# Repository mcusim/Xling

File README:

hardware
	3d_models	.STEP and .WRL model files for all footprints
	datasheets	data sheets for components used
	gerber		final production files
	images		SVG images and 3D board renders
	lib_sch		schematic symbols
	lib_fp.pretty	footprints
	pdf		schematics, board layouts, dimension drawings

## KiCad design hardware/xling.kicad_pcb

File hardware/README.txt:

3d_models	.STEP and .WRL model files for all footprints
datasheets	data sheets for components used
gerber		final production files
images		SVG images and 3D board renders
lib_sch		schematic symbols
lib_fp.pretty	footprints
pdf		schematics, board layouts, dimension drawings

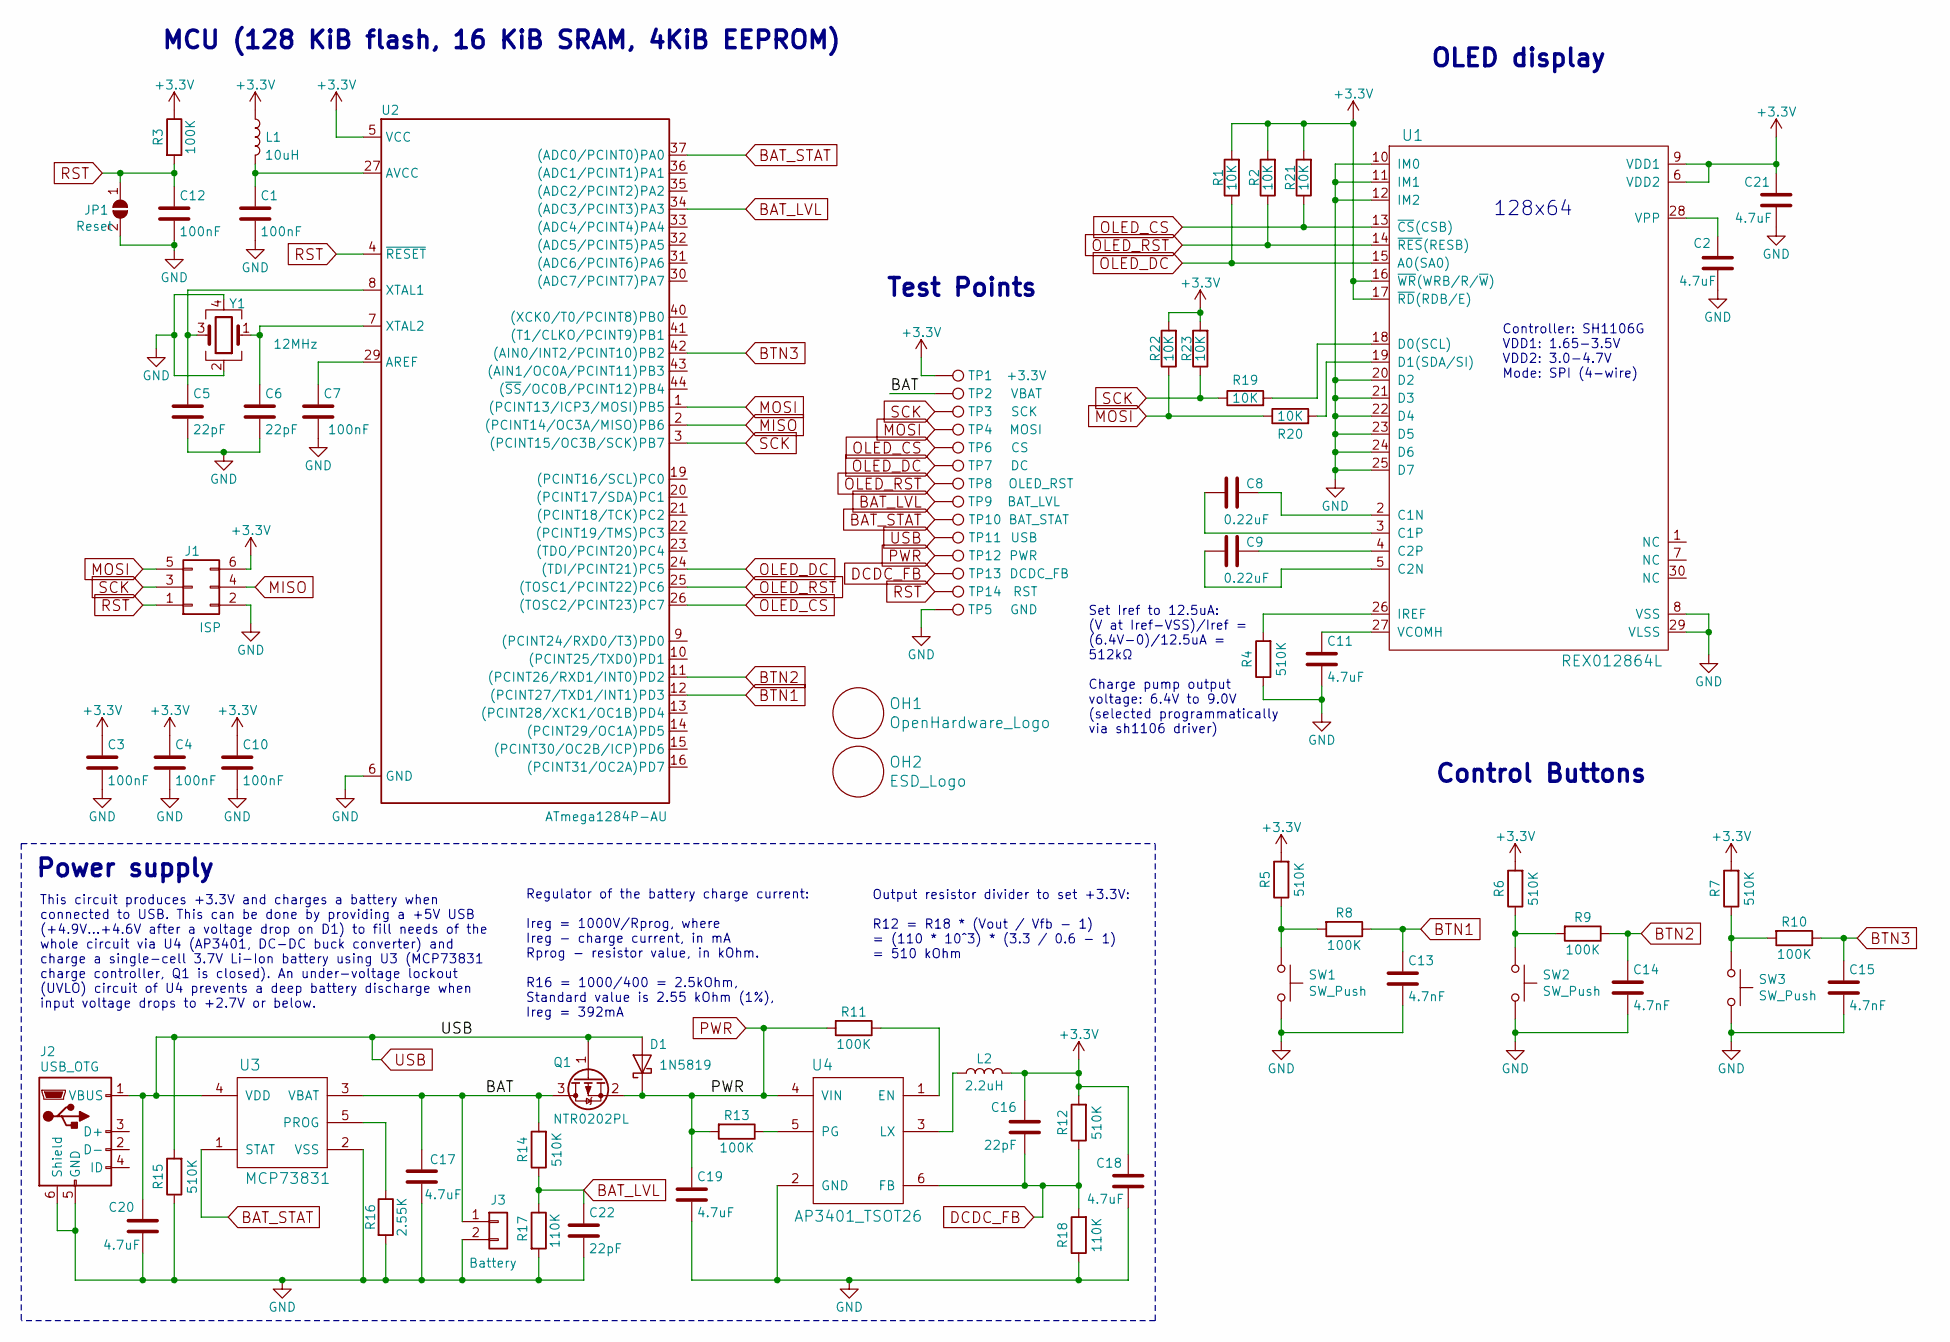
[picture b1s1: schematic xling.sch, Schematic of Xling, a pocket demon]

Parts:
C1, C3, C4, C7, C10, C12: 100nF; C_0603_1608Metric; MPN CL10B104KO8NNNC
C2, C11, C17, C18, C19, C20, C21: 4.7uF; C_0603_1608Metric; MPN CL10A475KQ8NNNC
C5, C6, C16, C22: 22pF; C_0603_1608Metric; MPN CL10C220JB8NNNC
C8, C9: 0.22uF; C_0603_1608Metric; MPN CL10B224KO8NNNC
C13, C14, C15: 4.7nF; C_0603_1608Metric; MPN CL10B472KB8NNNC
D1: 1N5819; D_SOD-123; MPN 1N5819HW-7-F
J1: ISP; Molex_Pico-Lock_504050-0691_1x06-1MP_P1.50mm_Horizontal; MPN 504050-0691
J2: USB_OTG; USB_Micro-B_Molex-105017-0001; MPN 105017-0001
J3: Battery; Battery_SMD_pads_1x02_HandSoldering; MPN N/A
JP1: Reset; SolderJumper-2_P1.3mm_Open_Pad1.0x1.5mm
L1: 10uH; L_1210_3225Metric; MPN B82422A1103K100
L2: 2.2uH; L_1210_3225Metric; MPN NLV32T-2R2J-PF
OH1: OpenHardware_Logo; OSHW-Logo_5.7x6mm_SilkScreen
OH2: ESD_Logo; ESD-Logo_6.6x6mm_SilkScreen
Q1: NTR0202PL; SOT-23; MPN NTR0202PLT1G
R1, R2, R19, R20, R21, R22, R23: 10K; R_0603_1608Metric; MPN 0603SAJ0103T5E
R3, R8, R9, R10, R11, R13: 100K; R_0603_1608Metric; MPN 0603SAJ0104T5E
R4, R5, R6, R7, R12, R14, R15: 510K; R_0603_1608Metric; MPN 0603SAJ0514T5E
R16: 2.55K; R_0603_1608Metric; MPN 0603SAF2551T5E
R17, R18: 110K; R_0603_1608Metric; MPN 0603SAF1103T5E
SW1, SW2, SW3: SW_Push; SW_Tact_4.5x4.5mm_TVCM09BB_Low_Profile; MPN TVCM09BB
TP1: +3.3V; TestPoint_Pad_D0.5mm
TP2: VBAT; TestPoint_Pad_D0.5mm
TP3: SCK; TestPoint_Pad_D0.5mm
TP4: MOSI; TestPoint_Pad_D0.5mm
TP5: GND; TestPoint_Pad_D1.0mm
TP6: CS; TestPoint_Pad_D0.5mm
TP7: DC; TestPoint_Pad_D0.5mm
TP8: OLED_RST; TestPoint_Pad_D0.5mm
TP9: BAT_LVL; TestPoint_Pad_D0.5mm
TP10: BAT_STAT; TestPoint_Pad_D0.5mm
TP11: USB; TestPoint_Pad_D0.5mm
TP12: PWR; TestPoint_Pad_D0.5mm
TP13: DCDC_FB; TestPoint_Pad_D0.5mm
TP14: RST; TestPoint_Pad_D0.5mm
U1: REX012864L; DisplayPin_1x30_P0.7mm; MPN REX012864LWAP3N00000
U2: ATmega1284P-AU; TQFP-44_10x10mm_P0.8mm; MPN ATMEGA1284P-AU
U3: MCP73831; MCP73831_SOT_23; MPN MCP73831T-2ATI/OT
U4: AP3401_TSOT26; MPN AP3401KTTR-G1
Y1: 12MHz; Crystal_SMD_CFPX-104-4Pin_5x3.2mm; MPN LFXTAL032878BULK

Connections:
+3V3: C3.1, C4.1, C10.1, C16.1, C18.1, C21.1, J1.6, L1.1, L2.2, R1.2, R2.2, R3.1, R5.2, R6.2, R7.2, R12.2, R21.2, R22.2, R23.2, TP1.1, U1.6 (VDD2), U1.9 (VDD1), U1.16 (~WR~(WRB/R/~W~)), U1.17 (~RD~(RDB/E)), U2.5 (VCC), U2.17 (VCC), U2.38 (VCC)
/BAT: C17.1, J3.1, Q1.3 (D), R14.2, TP2.1, U3.3 (VBAT)
BAT_LVL: C22.2, R14.1, R17.1, TP9.1, U2.34 ((ADC3/PCINT3)PA3)
BAT_STAT: TP10.1, U2.37 ((ADC0/PCINT0)PA0), U3.1 (STAT)
BTN1: C13.1, R8.1, U2.12 ((PCINT27/TXD1/INT1)PD3)
BTN2: C14.1, R9.1, U2.11 ((PCINT26/RXD1/INT0)PD2)
BTN3: C15.1, R10.1, U2.42 ((AIN0/INT2/PCINT10)PB2)
DCDC_FB: C16.2, R12.1, R18.2, TP13.1, U4.6 (FB)
GND: C1.2, C2.2, C3.2, C4.2, C5.1, C6.1, C7.2, C10.2, C11.2, C12.2, C13.2, C14.2, C15.2, C17.2, C18.2, C19.2, C20.2, C21.2, C22.1, J1.2, J2.5 (GND), J2.6 (Shield), J3.2, JP1.2 (B), R4.1, R15.1, R16.2, R17.2, R18.1, SW1.2, SW2.2, SW3.2, TP5.1, U1.8 (VSS), U1.10 (IM0), U1.11 (IM1), U1.12 (IM2), U1.20 (D2), U1.21 (D3), U1.22 (D4), U1.23 (D5), U1.24 (D6), U1.25 (D7), U1.29 (VLSS), U2.6 (GND), U2.18 (GND), U2.28 (GND), U2.39 (GND), U3.2 (VSS), U4.2 (GND), Y1.2, Y1.4
MISO: J1.4, U2.2 ((PCINT14/OC3A/MISO)PB6)
MOSI: J1.5, R20.1, R22.1, TP4.1, U2.1 ((PCINT13/ICP3/MOSI)PB5)
unnamed: C1.1, L1.2, U2.27 (AVCC)
unnamed: C2.1, U1.28 (VPP)
unnamed: C5.2, U2.8 (XTAL1), Y1.3
unnamed: C6.2, U2.7 (XTAL2), Y1.1
unnamed: C7.1, U2.29 (AREF)
unnamed: C8.1, U1.2 (C1N)
unnamed: C8.2, U1.3 (C1P)
unnamed: C9.1, U1.4 (C2P)
unnamed: C9.2, U1.5 (C2N)
unnamed: C11.1, U1.27 (VCOMH)
unnamed: L2.1, U4.3 (LX)
unnamed: R4.2, U1.26 (IREF)
unnamed: R5.1, R8.2, SW1.1
unnamed: R6.1, R9.2, SW2.1
unnamed: R7.1, R10.2, SW3.1
unnamed: R11.1, U4.1 (EN)
unnamed: R13.1, U4.5 (PG)
unnamed: R16.1, U3.5 (PROG)
unnamed: R19.2, U1.18 (D0(SCL))
unnamed: R20.2, U1.19 (D1(SDA/SI))
OLED_CS: R21.1, TP6.1, U1.13 (~CS~(CSB)), U2.26 ((TOSC2/PCINT23)PC7)
OLED_DC: R1.1, TP7.1, U1.15 (A0(SA0)), U2.24 ((TDI/PCINT21)PC5)
OLED_RST: R2.1, TP8.1, U1.14 (~RES~(RESB)), U2.25 ((TOSC1/PCINT22)PC6)
PWR: C19.1, D1.1 (K), Q1.2 (S), R11.2, R13.2, TP12.1, U4.4 (VIN)
RST: C12.1, J1.1, JP1.1 (A), R3.2, TP14.1, U2.4 (~RESET)
SCK: J1.3, R19.1, R23.1, TP3.1, U2.3 ((PCINT15/OC3B/SCK)PB7)
USB: C20.1, D1.2 (A), J2.1 (VBUS), Q1.1 (G), R15.2, TP11.1, U3.4 (VDD)

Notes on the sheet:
Power supply
Controller: SH1106G VDD1: 1.65-3.5V VDD2: 3.0-4.7V Mode: SPI (4-wire)
Output resistor divider to set +3.3V: R12 = R18 * (Vout / Vfb - 1) = (110 * 10^3) * (3.3 / 0.6 - 1) = 510 kOhm
OLED display
Control Buttons
128x64
MCU (128 KiB flash, 16 KiB SRAM, 4KiB EEPROM)
Test Points
This circuit produces +3.3V and charges a battery when connected to USB. This can be done by providing a +5V USB (+4.9V...+4.6V after a voltage drop on D1) to fill needs of the whole circuit via U4 (AP3401, DC-DC buck converter) and charge a single-cell 3.7V Li-Ion battery using U3 (MCP73831 charge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
Set Iref to 12.5uA: (V at Iref-VSS)/Iref = (6.4V-0)/12.5uA = 512kΩ Charge pump output voltage: 6.4V to 9.0V (selected programmatically via sh1106 driver)
Regulator of the battery charge current: Ireg = 1000V/Rprog, where Ireg - charge current, in mA Rprog - resistor value, in kOhm. R16 = 1000/400 = 2.5kOhm, Standard value is 2.55 kOhm (1%), Ireg = 392mA

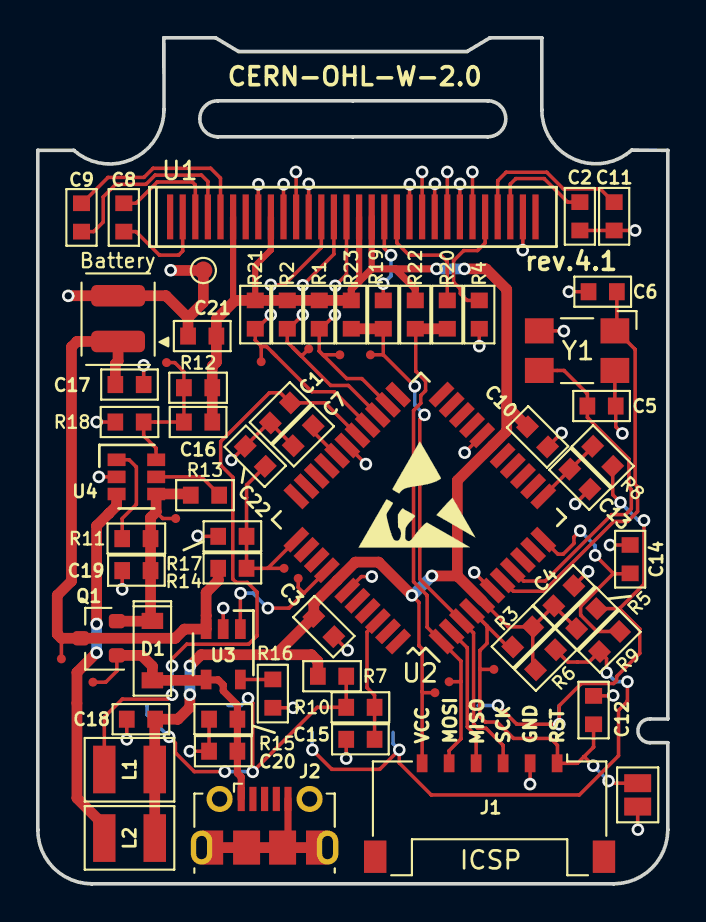
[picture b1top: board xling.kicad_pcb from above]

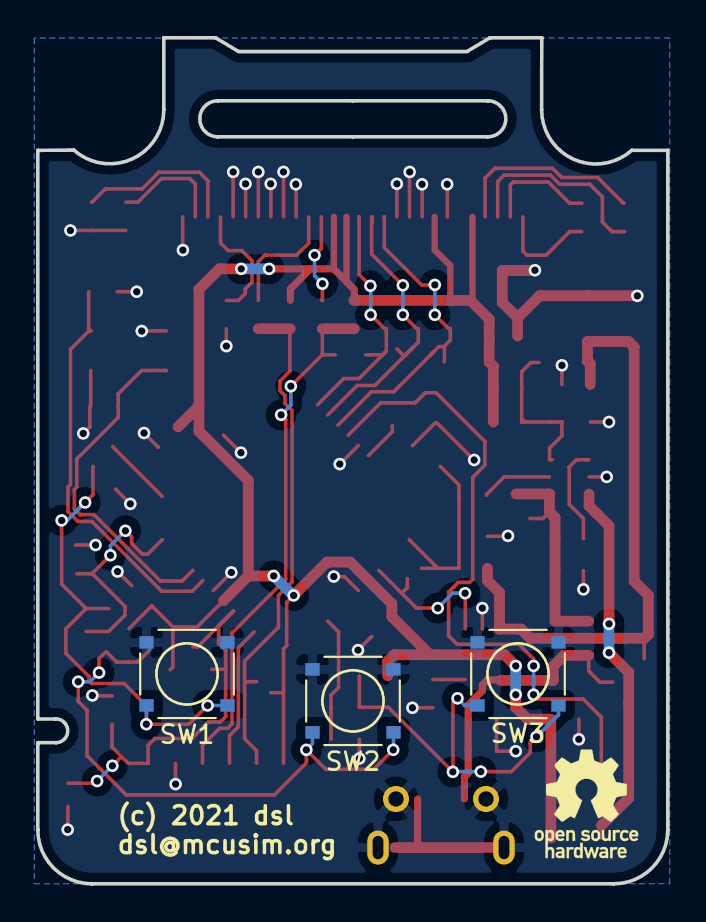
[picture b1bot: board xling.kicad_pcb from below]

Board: 2 copper layers, 35.0 x 47.0 mm, 77 parts (4 on the bottom side), 38 nets.

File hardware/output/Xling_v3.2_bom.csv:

/home/dsl/git/Xling/xling.sch,,,,,,,
Sat 21 Mar 2020 05:07:58 PM CET,,,,,,,
Eeschema 5.1.5-52549c5~84~ubuntu18.04.1,,,,,,,
Revision: 3.2,,,,,,,
Component Count: 69,,,,,,,
Ref,Qnty,Value,Part,Footprint,Description,Vendor,Model
"C1, C3, C4, C7, C10, C12",6,100nF,xling:C,Xling Footprints:C_0603_1608Metric,,,CL10B104KO8NNNC
"C2, C11, C17, C18, C19, C20, C21",7,4.7uF,xling:C,Xling Footprints:C_0603_1608Metric,,,CL10A475KQ8NNNC
"C5, C6, C16, C22",4,22pF,xling:C,Xling Footprints:C_0603_1608Metric,,,CL10C220JB8NNNC
"C8, C9",2,0.22uF,xling:C,Xling Footprints:C_0603_1608Metric,,,CL10B224KO8NNNC
"C13, C14, C15",3,4.7nF,xling:C,Xling Footprints:C_0603_1608Metric,,,CL10B472KB8NNNC
D1,1,1N5819,xling:1N5818,Xling Footprints:D_SOD-123,,,1N5819HW-7-F
J1,1,ISP,xling:Conn_02x03_Odd_Even,Xling Footprints:Molex_Pico-Lock_504050-0691_1x06-1MP_P1.50mm_Horizontal,,,504050-0691
J2,1,USB_OTG,xling:USB_OTG,Xling Footprints:USB_Micro-B_Molex-105017-0001,,,105017-0001
J3,1,Battery,xling:Conn_01x02,Xling Footprints:Battery_SMD_pads_1x02_HandSoldering,,,
L1,1,10uH,xling:L,Xling Footprints:L_1210_3225Metric,,,B82422A1103K100
L2,1,2.2uH,xling:L,Xling Footprints:L_1210_3225Metric,,,NLV32T-2R2J-PF
OH1,1,OpenHardwareLogo,xling:OpenHardwareLogo,Xling Footprints:oshw,,,
Q1,1,NTR0202PL,xling:NTR2101P,Xling Footprints:SOT-23,,,NTR0202PLT1G
"R1, R2, R19, R20, R21, R22, R23",7,10K,xling:R,Xling Footprints:R_0603_1608Metric,,,0603SAJ0103T5E
"R3, R8, R9, R10, R11, R13",6,100K,xling:R,Xling Footprints:R_0603_1608Metric,,,0603SAJ0104T5E
"R4, R5, R6, R7, R12, R14, R15",7,510K,xling:R,Xling Footprints:R_0603_1608Metric,,,0603SAJ0514T5E
R16,1,2.55K,xling:R,Xling Footprints:R_0603_1608Metric,,,0603SAF2551T5E
"R17, R18",2,110K,xling:R,Xling Footprints:R_0603_1608Metric,,,0603SAF1103T5E
"SW1, SW2, SW3",3,BTN,xling:SW_Push,Xling Footprints:SW_Tact_4.5x4.5mm_TVCM09BB_Low_Profile,,,TVCM09BB
U1,1,REX012864L,xling:REX012864L,Xling Footprints:DisplayPin_1x30_P0.7mm,,,REX012864LYAP3N00000
U2,1,ATmega1284P-AU,xling:ATmega1284P-AU,Xling Footprints:TQFP-44_10x10mm_P0.8mm,"20MHz, 128kB Flash, 16kB SRAM, 4kB EEPROM, JTAG, TQFP-44",,ATMEGA1284P-AU
U3,1,MCP73831,xling:MCP73831,Xling Footprints:MCP73831_SOT_23,,,MCP73831T-2ATI/OT
U4,1,AP3401_TSOT26,xling:AP3401_TSOT26,Xling Footprints:AP3401_TSOT26,"1.5MHz, 1A DC-DC Buck Converter",,AP3401KTTR-G1
Y1,1,12MHz,xling:Crystal_GND24,Xling Footprints:Crystal_SMD_CFPX-104-4Pin_5x3.2mm,"Four pin crystal, GND on pins 2 and 4",,LFXTAL032878BULK

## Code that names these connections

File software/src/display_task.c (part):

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#define CLEAR_BIT(byte, bit)	((byte) &= (uint8_t) ~(1U << (bit)))
#define TNAME			"Display Task"
#define STSZ			(configMINIMAL_STACK_SIZE)
#define OLED_DC			PC5		/* OLED Data/Command pin. */
#define OLED_RST		PC6		/* OLED Reset pin. */
#define OLED_CS			PC7		/* OLED Chip Select pin. */
#define OLED_MOSI		PB5		/* OLED SPI pin. */
#define OLED_MISO		PB6		/* OLED SPI pin. */
#define OLED_SCK		PB7		/* OLED SPI pin. */
#define BLINK_DELAY		49
#define LOOK_AT_DELAY		19

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	uint8_t col = 0;
	uint8_t skip_bat_lvl = 0;
	uint16_t bat_lvl = UINT16_MAX;
	uint16_t bat_stat = 5;
	uint16_t blink_delay = BLINK_DELAY;
	uint16_t look_at_delay = LOOK_AT_DELAY;
	char textbuf[32];
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
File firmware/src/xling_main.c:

/*
 * Copyright (c) 2017, 2018, The MCUSim Contributors
 * All rights reserved.
 *
 * Redistribution and use in source and binary forms, with or without
 * modification, are permitted provided that the following conditions are met:
 *     * Redistributions of source code must retain the above copyright
 *       notice, this list of conditions and the following disclaimer.
 *     * Redistributions in binary form must reproduce the above copyright
 *       notice, this list of conditions and the following disclaimer in the
 *       documentation and/or other materials provided with the distribution.
 *     * Neither the name of the MCUSim or its parts nor the
 *       names of its contributors may be used to endorse or promote products
 *       derived from this software without specific prior written permission.
 * THIS SOFTWARE IS PROVIDED BY THE COPYRIGHT HOLDERS AND CONTRIBUTORS "AS IS"
 * AND ANY EXPRESS OR IMPLIED WARRANTIES, INCLUDING, BUT NOT LIMITED TO,
 * THE IMPLIED WARRANTIES OF MERCHANTABILITY AND FITNESS FOR A PARTICULAR
 * PURPOSE ARE DISCLAIMED. IN NO EVENT SHALL COPYRIGHT HOLDER OR CONTRIBUTORS
 * BE LIABLE FOR ANY DIRECT, INDIRECT, INCIDENTAL, SPECIAL, EXEMPLARY, OR
 * CONSEQUENTIAL DAMAGES (INCLUDING, BUT NOT LIMITED TO, PROCUREMENT OF
 * SUBSTITUTE GOODS OR SERVICES; LOSS OF USE, DATA, OR PROFITS; OR BUSINESS
 * INTERRUPTION) HOWEVER CAUSED AND ON ANY THEORY OF LIABILITY, WHETHER IN
 * CONTRACT, STRICT LIABILITY, OR TORT (INCLUDING NEGLIGENCE OR OTHERWISE)
 * ARISING IN ANY WAY OUT OF THE USE OF THIS SOFTWARE, EVEN IF ADVISED OF THE
 * POSSIBILITY OF SUCH DAMAGE.
 *
 * Main file of the Xling firmware.
 */
#define F_CPU			12000000UL	/* CPU clock frequency */
#define TWI_CLOCK		400000L		/* TWI clock frequency */

#include <stdint.h>
#include <stdio.h>
#include <limits.h>
#include <avr/io.h>
#include <avr/interrupt.h>
#include <avr/pgmspace.h>
#include <util/delay.h>

#include "xling/twi.h"
#include "xling/luci.h"
#include "xling/hw/ssd1309.h"

#define SET_BIT(byte, bit)	((byte)|=(1UL<<(bit)))
#define CLEAR_BIT(byte, bit)	((byte)&=~(1UL<<(bit)))
#define IS_SET(byte, bit)	(((byte)&(1UL<<(bit)))>>(bit))

#define BTN1			PD0
#define BTN2			PD1
#define BTN3			PD2
#define OLED_RES		PD3
#define OLED_PWR		PD4

#define FRAME_ITER		5
#define FRAME_DIV		100000UL

/* Static variables */
static struct XG_TWI twi;
static struct XG_SSD1309 display;
static volatile uint32_t ms = 0;

/* Declarations of the local functions */
static void timer2_init(void);

int main(void)
{
	uint32_t i, j, frames;
	uint32_t delay_ms;
	char textbuf[32];

	/* Bit-bang TWI configuration */
	twi.port = (uint8_t *)0x28;	/* Offset to PORTC register */
	twi.ddr = (uint8_t *)0x27;	/* Offset to DDRC register */
	twi.sda = PC4;
	twi.scl = PC5;
	XG_TWIInit(&twi, 0x7A, F_CPU, TWI_CLOCK);

	/* Configure pins as input/output ones. */
	DDRD = 0x00;
	SET_BIT(DDRD, OLED_RES);		/* output */
	SET_BIT(DDRD, OLED_PWR);		/* output */
	CLEAR_BIT(DDRD, BTN1);			/* input */
	CLEAR_BIT(DDRD, BTN2);			/* input */
	CLEAR_BIT(DDRD, BTN3);			/* input */

	/* Set initial values. */
	SET_BIT(PORTD, OLED_RES);
	CLEAR_BIT(PORTD, OLED_PWR);
	_delay_ms(1);

	/* We've to switch OLED on. */
	CLEAR_BIT(PORTD, OLED_RES);
	_delay_ms(1);
	SET_BIT(PORTD, OLED_RES);
	_delay_ms(1);
	SET_BIT(PORTD, OLED_PWR);
	_delay_ms(100);
	/* Setup OLED display */
	XG_SSD1309TWIInit(&twi, &display);

	/* Setup Timer/Counter2 to count milliseconds */
	timer2_init();
	sei();

	i = 0;
	while (1) {
		XG_SSD1309SetPage(&display, 0);
		XG_SSD1309SetColumn(&display, 0);

		XG_TWIStart(&twi);
		XG_TWIWrite(&twi, 0x40);
		delay_ms = ms;
		for (j = 0; j < FRAME_ITER; j++) {
			for (i = 0; i < sizeof oled_luci; i++) {
				XG_TWIWrite(&twi, pgm_read_byte(&oled_luci[i]));
			}
		}
		delay_ms = ms-delay_ms;
		XG_TWIStop(&twi);

		snprintf(textbuf, sizeof textbuf, "%lu.%lu",
		         FRAME_DIV/delay_ms, FRAME_DIV%delay_ms);
		XG_SSD1309SetPage(&display, 7);
		XG_SSD1309SetColumn(&display, 0);
		XG_SSD1309Print(&display, &textbuf[0]);
		_delay_ms(300);
	}
	return 0;
}

static void timer2_init(void)
{
	/* CTC mode, WGM22:0 = 2 */
	TCCR2A |= (1<<WGM21);
	TCCR2A &= ~(1<<WGM20);
	TCCR2B &= ~(1<<WGM22);

	/* OCR2A is 124 to gain 1kHz with selected prescaler */
	TCNT2 = 0;
	OCR2A = 124;
	/* Enable interrupt */
	TIMSK2 |= (1<<OCIE2A);

	/* Start timer, prescaler to Fclk_io/32: CS21:0 = 6 */
	TCCR2B |= (1<<CS21) | (1<<CS20);
	TCCR2B &= ~(1<<CS22);
}

ISR(TIMER2_COMPA_vect)
{
	ms++;
}

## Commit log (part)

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2017-11-07 patch 0.1.0: Initial Xling schematic.
2017-11-07 patch 0.1.1: Add missing component values in schematic.
2017-11-08 patch 0.1.2: Schematic update with assigned footprints.
2017-11-09 patch 0.1.3: Add library with footprints.
2017-11-09 patch 0.1.4: Add footprint for MCP73831.
2017-11-09 patch 0.1.5: Add footprint for TPS63031.
2017-11-10 patch 0.1.6: Add footprint for ATmega128L.
2017-11-11 patch 0.1.7: Early prototype of the board.
2017-11-14 patch 0.1.8: Add other OLED and DCDC 3V-to-12V.
2017-11-18 patch 0.1.10: First PCB prototype.
2017-11-18 patch 0.1.11: Add OSHW and 1KIB logos to the PCB.
2017-11-18 patch 0.1.12: Remove all dummy elements from PCB design.
2017-11-19 patch 0.1.13: Adjust silk screen text to include into Gerber files.
2017-11-25 Add gerber files for xling-0.1.13.
2017-11-25 patch 0.1.14: Add additional measurements to PCB.
2017-12-25 patch 0.1.15: Fix battery charging scheme.
2018-01-19 patch 0.1.16: Add 'Model' field to all schematic components to point selected model clearly.
2018-01-23 patch 0.1.17: Add 3.3V linear regulator for USB mode.
    - Fix placement of U1 (mirrored);
    - Fix placement of the AVR ISR connector;
    - Adjust U3 pads to easy soldering (they are a bit bigger now);
    - Add marks for D1 and D2 LEDs;
    - Replace models of several components to be in 0805 or 0603 cases;
    - Add fixed linear 3.3V voltage regulator for USB mode;
2018-04-20 patch 0.1.18: Add new KiCad modules and scheme changes.
2018-04-20 patch 0.1.19: Add shared directory with SPICE models for MOSFETs.
2018-05-27 patch 0.1.20: Update PCB and prepare gerber files for production.
2018-06-24 patch 0.1.21: Correct exact models of the components in schematic.
2018-07-12 patch 0.1.22: Power supply scheme modified and PCB update.
2018-11-02 patch 0.2.0: Update hardware files to KiCad 5.
    This patch brought a firmware part of the project to perform any tests
    only. It draws two different pictures on an OLED display and counts
    frames per second.
    Schematic was updated to include a new DC-DC buck converter (AP3401) to
    produce 3.3V from both USB and a battery. Choosing this converter is a
    trade-off between an expensive buck-boost converter which can operate
2018-11-02 patch 0.2.0001: Adjust some footprints.
    Several footprints were updated to use rounded rectangles instead of
    rectangles with sharp corners as pads.
    BOM generator script updated to include a revision into a BOM html file.
    It is useful to understand which components are required for a specific
    version of the device.
    There is a new TSOT26 footprint created and added especially for AP3401
2018-11-03 patch 0.2.0002: Update PCB.
    Components placed according to their updated footprints. The most
    noticible ones are IDC connecter of the AVR ISP and a horizontal battery
    connector. There are many minor changes and no routing yet.
2018-11-04 patch 0.2.0004: Updated footprints.
    Several footprints were updated to replaced rectangle pads with
    rounded-corner pads. Minor PCB changes were made also.
    Bill of materials can be found in the hardware directory.
2019-03-30 patch 0.2.5: New OLED.
    There is a huge change in a circuit to replace an OLED and fix multiple
    mistakes and improve it a bit.
2019-04-01 patch 0.2.6: Update and add missing footprints.
    ticket: N/A
    There new models/parts found for micro switches and a connector for AVR
    in-circuit system programmer.
2019-04-04 patch 0.2.7: PCB adjustments.
    ticket: N/A
    There are some modifications to make a new version of the PCB ready for
    manufacturing.
2019-04-04 patch 0.2.8: Add micro USB 3D model.
    ticket: N/A
2019-04-04 patch 0.2.9: New battery SMD footprint.
    ticket: N/A
2019-04-04 patch 0.2.10: Add gaps to mount PCB correctly.
    ticket: N/A
2019-04-04 patch 0.2.11: Little adjustments to schematic.
2019-04-05 patch 0.2.12: Make a gap for OLED FFC bigger.
    ticket: N/A
    There is also a 3D package for Molex PicoFlex connector for AVR ISP.
2019-04-05 patch 0.2.14: Add board info and a name (silk).
    ticket: N/A
2019-04-05 patch 0.2.15: Remove unused gap on PCB.
    ticket: N/A
2019-04-19 patch 0.2.16: Fix crystal footprint.
    There are multiple fixes and adjustments performed. Among the others:
    - Battery footprint improved to better wiring and soldering;
    - Silkscreen fixed on the many footprints (including 0603 caps and res);
    - Crystal footprint fixed;
    - Test points for the GND, +3.3V and Vbat added.
2019-06-17 patch 0.2.17: New commands for SH1106-based OLED.
    Firmware has been modified to support commands for SH1106 OLED
    controller.
    There is also a change to send TWI commands in batch.
2019-09-19 patch 0.3: A new ATmega1284p-based PCB.
    This is a new version of the whole board which is based on ATmega1284p
    now. The most noticible changes:
    - A new ATmega1284p microcontroller (128 KiB flash, 16 KiB SRAM),
    - OLED is connected via 3-wire SPI (instead of I2C earlier),
    - A new version of PCB has been re-routed from scratch,
    - An artwork for a bottom PCB layer provided by SierraSaura
2019-11-17 patch 3.1: More checkpoints and 4-wire SPI.
    This is the first commit after version adjustment and in a new
    current/3.0 branch. All of the changes in the third iteration of the
    Xling PCB will find their place in this branch.
    Starting from Xling PCB v3.1, new checkpoints are available:
    +3.3V - output voltage of the power supply block and AP3401
    particularly;
2020-01-16 patch 3.2: Minor PCB changes.
    - Buttons are placed according to the new case configuration;
    - BTN3 pin assigned to pin 42 (INT2) of the MCU;
    - A new silkscreen artwork based on U2Pi's work from deviantart;
    - A narrow deeping on the left is a bit wider;
2020-03-27 Road to OSHWA certification.
    This is the first commit in the current/4.0 branch which brings a lot of
    changes which are supposed to gather all files in one place and open a road
    to OSHWA certification.
    Structure of the repository changed. It contains all of the necessary
    design documents, firmware source code and other files to let everyone
    make the device.
2020-03-29 Update labels on silkscreen.
    Size and position of the silkscreen text have been adjusted to improve
    readability.
2020-03-29 Switch to tasks notification API.
    Problem:
    Xling hangs from time to time during wake ups. There are no display updates
    via SPI either (checked by Saleae Logic 8).
    Solution:
    Get rid of the direct control functions to manipulate the tasks like
    vTaskSuspend() and vTaskResume() in favor of the tasks notification API
2020-05-15 Graphics API function to paint images on a canvas.
    Problem:
    There is a need for a function to paint images at the arbitrary
    coordinates on a canvas which can be transferred to the OLED
    display. It could help to develop graphics engine for Xling also.
    Solution:
    A new MSIM_SH1106_Draw_PF() function which allows to paint an image
2020-05-19 Tweak task priorities to avoid display freezing.
    Problem:
    Xling tends to freeze updates of the display with the previous
    version of the firmware.
    Solution:
    Priorities of the Sleep Mode and Battery Monitor tasks have been
    lowered by 1, and all of the tasks with their priorities look like:
2020-07-12 Tweaks to paint text with different fonts.
    Problem:
    It might be necessary to paint text with different fonts generated by
    LCD Image Converter.
    Solution:
    There is a specific font template prepared for LCD Image Converter
    (see common/lcd-image-converter/Xling_font_template.tmpl). Several tweaks
2020-09-06 Plugin for GIMP to export image as a scene.
    Problem:
    Composing new scenes for Xling takes time to finish it manually.
    It might also be useful to design scenes for Xling visually using GIMP,
    for example.
    Solution:
    Plugin for GNU Image Manipulation Program (GIMP) to export an existing
2020-09-12 Update Xling PCB to revision 4.
    Problem:
    It's hard to solder battery pads on the previous versions of the Xling
    PCB. Battery pins can easily be shorted and the battery itself might be
    damaged.
    Buttons in the previous revision can also be damaged easily because of
    the membrane which can be ripped off.
2020-09-12 Add license for the case files.
2020-09-12 Add a guide for CERN-OHL-W-2.0.
2020-09-17 WIP to support animations in Xlingtool.
    Problem:
    Xlingtool, a plugin for GIMP, doesn't have a way to define and
    export animations in scenes for Xling.
    Solution:
    Work-in-progress for Xlingtool to implement an ability to
    define and link animation frames together in order to export them as
2020-09-20 WIP to support animations in Xlingtool.
    Updates:
    It is possible to parse animations frames (defined as ordinary
    layers in GIMP) marked with !anim() and !go tags. These frames are
    combined into paths which form animations themselves.
    For example, common/images/scenes/smoking_02.xcf contains two
    animations:
2020-09-23 WIP to support animations in Xlingtool.
    Updates:
    It is possible to track indexes of the frames within animation which
    will help to export animations to Xling firmware easily.
2020-09-26 WIP to support animations in Xlingtool.
    Updates:
    Xlingtool can export a header file (anim.h) which contains
    definitions of all animations used in the current scene.
    Scene layers are tracked separately in _scene_layers array. They
    usually contain names of the animations and hashes of the static
    images.
2021-01-01 Animations and keyboard callback in Xlingtool.
    Updates:
    Xlingtool, a plugin for GIMP to export scenes for Xling, can process
    several new tags from the layer names including:
    - !anim(anim_name, anim_path)
    - !stay(frames_to_stay)
    - !go(anim_path, chance_to_go)
2021-01-02 !inactive() tag added to disable animations.
    Updates:
    It might be necessary to enable/disable animations in a scene in
    runtime. !inactive() helps to do so. All of the animations are
    enabled by default unless !inactive() tag added to any of the
    animation's frames.
    Animation itself can be enabled in runtime by setting its "active"
2021-01-10 XG_Draw_PF() can draw an image at the negative coordinates.
    Problem:
    It's impossible to use negative coordinates as a top-left
    corner of the image to draw on a canvas using XG_Draw_PF()
    function. However, it might be necessary for complex scenes
    with a plenty of animations and interactive parts.
    Solution:
2021-01-13 A finished "smoking_02" scene.
    There is a common/images/scenes/smoking_02.xcf finished, exported
    using Xlingtool and added to the project in
    software/include/xling/scenes.
    Another important change is a FreeRTOS kernel tick rate changed from
    1000 Hz to 500 Hz. It doesn't affect a behavior of the whole device,
    but allows to waste less time on context switches.
2021-04-04 Update Xling schematic and PCB to v4.1.
    Problem:
    There were too many routes in the ground copper layer which
    formed an obstacle for return currents. Molex Pico-EZmate header
    (2026560021) proved to be easy to solder, but really hard to
    solder battery pins for it.
    Solution:
2021-04-09 Export several scenes together by Xlingtool plugin.
    Problem:
    GIMP can have several images (scenes) opened, but only current
    one is exported by Xlingtool previously. It is a problem when
    several scenes have been prepared for Xling and should be
    exported together into anim.h and scenes.h files.
    Solution:
2021-04-11 Process groups of layers in Xlingtool.
    Problem:
    GIMP supports groups of layers, i.e. specific type which
    allows to combine relative layers together. It might
    simplify Xling scenes creation by grouping animations, static
    things and controls together, but Xlingtool didn't go through
    these layers recursively.

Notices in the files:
software/src/display_task.c:
SPDX-License-Identifier: GPL-3.0-or-later
Copyright (c) 2019 Dmitry Salychev
Xling firmware is free software: you can redistribute it and/or modify
it under the terms of the GNU General Public License as published by
the Free Software Foundation, either version 3 of the License, or
(at your option) any later version.
hardware/xling.kicad_pcb:
Licensed under CERN-OHL-W-2.0
Copyright (c) 2021 Dmitry Salychev
(c) 2021 dsl
